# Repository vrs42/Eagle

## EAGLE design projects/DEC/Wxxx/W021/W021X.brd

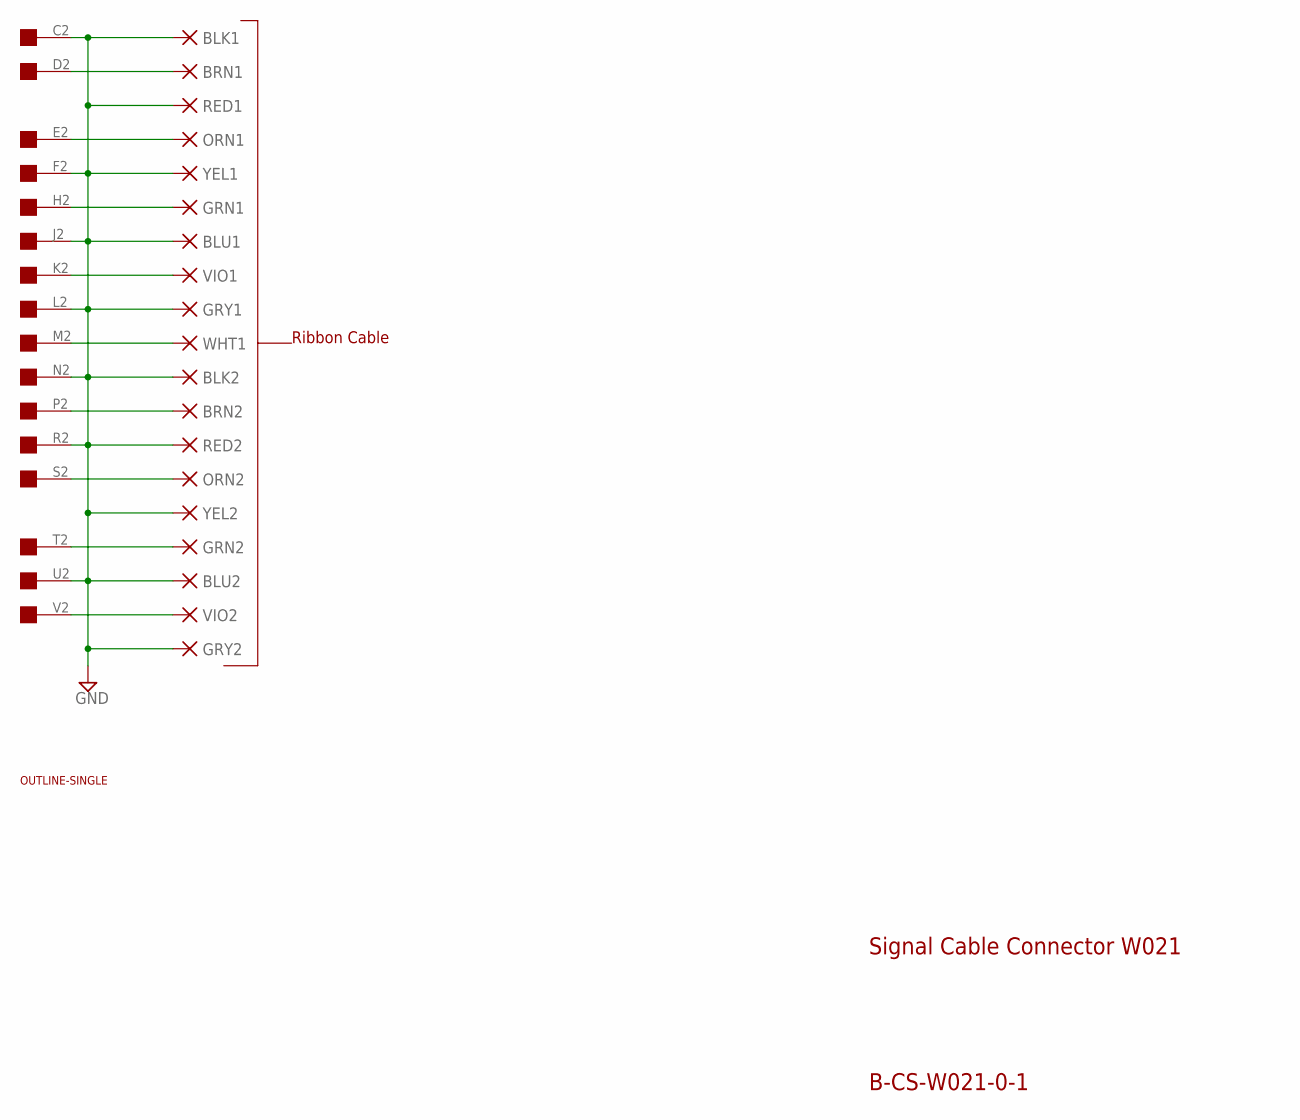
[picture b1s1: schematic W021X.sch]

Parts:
BLK1, BLK2: PAD-0465; 0465
BLU1, BLU2: PAD-0465; 0465
BRN1, BRN2: PAD-0465; 0465
GRN1, GRN2: PAD-0465; 0465
GRY1, GRY2: PAD-0465; 0465
ORN1, ORN2: PAD-0465; 0465
RED1, RED2: PAD-0465; 0465
U$1: OUTLINE-SINGLE; SINGLE
U$2: EDGE-1; EDGE-CON1
VIO1, VIO2: PAD-0465; 0465
WHT1: PAD-0465; 0465
YEL1, YEL2: PAD-0465; 0465

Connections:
GND: BLK1.P$1, BLK2.P$1, BLU1.P$1, BLU2.P$1, GRY1.P$1, GRY2.P$1, RED1.P$1, RED2.P$1, U$2.C2, U$2.F2, U$2.J2, U$2.L2, U$2.N2, U$2.R2, U$2.U2, YEL1.P$1, YEL2.P$1
unnamed: ORN1.P$1, U$2.E2
unnamed: GRN1.P$1, U$2.H2
unnamed: U$2.K2, VIO1.P$1
unnamed: U$2.M2, WHT1.P$1
unnamed: BRN2.P$1, U$2.P2
unnamed: ORN2.P$1, U$2.S2
unnamed: GRN2.P$1, U$2.T2
unnamed: U$2.V2, VIO2.P$1
unnamed: BRN1.P$1, U$2.D2

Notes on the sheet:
Signal Cable Connector W021
B-CS-W021-0-1
Ribbon Cable

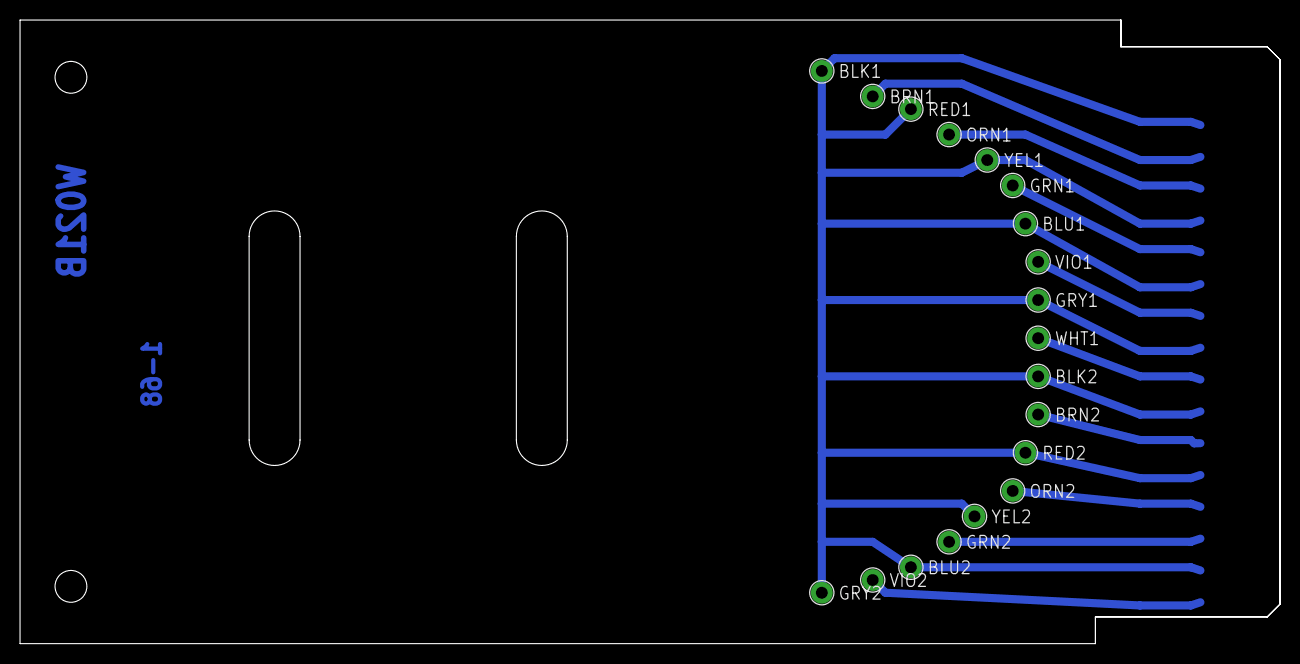
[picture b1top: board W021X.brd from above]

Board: 2 copper layers, 125.7 x 62.2 mm, 21 parts (0 on the bottom side), 10 nets.

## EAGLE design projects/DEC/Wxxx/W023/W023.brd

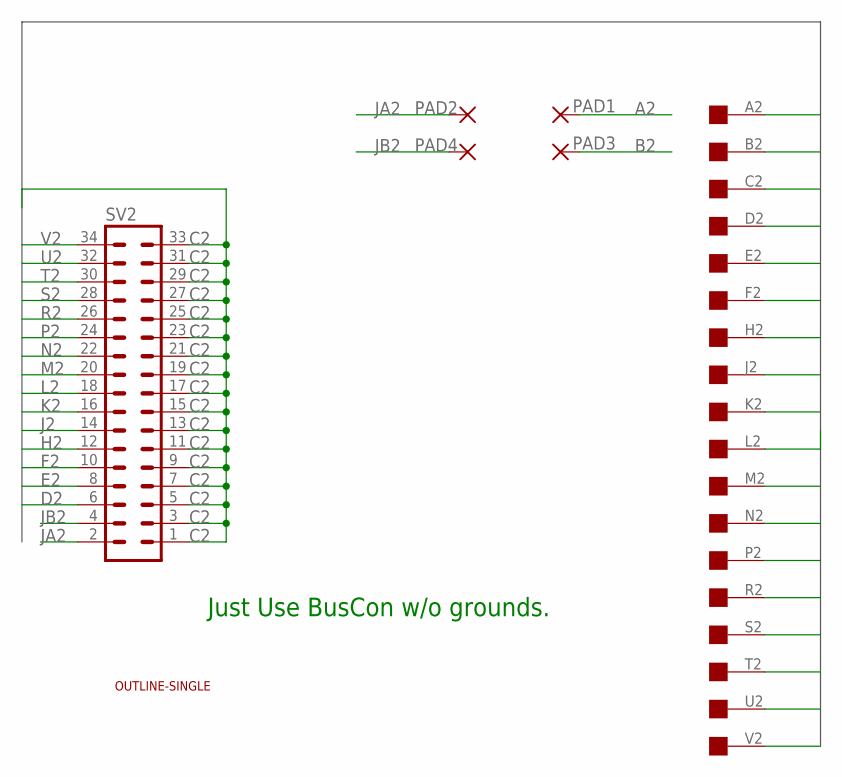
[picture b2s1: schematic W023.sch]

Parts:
PAD1, PAD2, PAD3, PAD4: 1,6/0,8
SV2: MA17-2
U$1: EDGE-1; EDGE-CON1
U$2: OUTLINE-SINGLE; SINGLE

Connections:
A2: PAD1.1, U$1.A2
B2: PAD3.1, U$1.B2
C2: SV2.1, SV2.3, SV2.5, SV2.7, SV2.9, SV2.11, SV2.13, SV2.15, SV2.17, SV2.19, SV2.21, SV2.23, SV2.25, SV2.27, SV2.29, SV2.31, SV2.33, U$1.C2
D2: SV2.6, U$1.D2
E2: SV2.8, U$1.E2
F2: SV2.10, U$1.F2
H2: SV2.12, U$1.H2
J2: SV2.14, U$1.J2
JA2: PAD2.1, SV2.2
JB2: PAD4.1, SV2.4
K2: SV2.16, U$1.K2
L2: SV2.18, U$1.L2
M2: SV2.20, U$1.M2
N2: SV2.22, U$1.N2
P2: SV2.24, U$1.P2
R2: SV2.26, U$1.R2
S2: SV2.28, U$1.S2
T2: SV2.30, U$1.T2
U2: SV2.32, U$1.U2
V2: SV2.34, U$1.V2

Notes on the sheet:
Just Use BusCon w/o grounds.

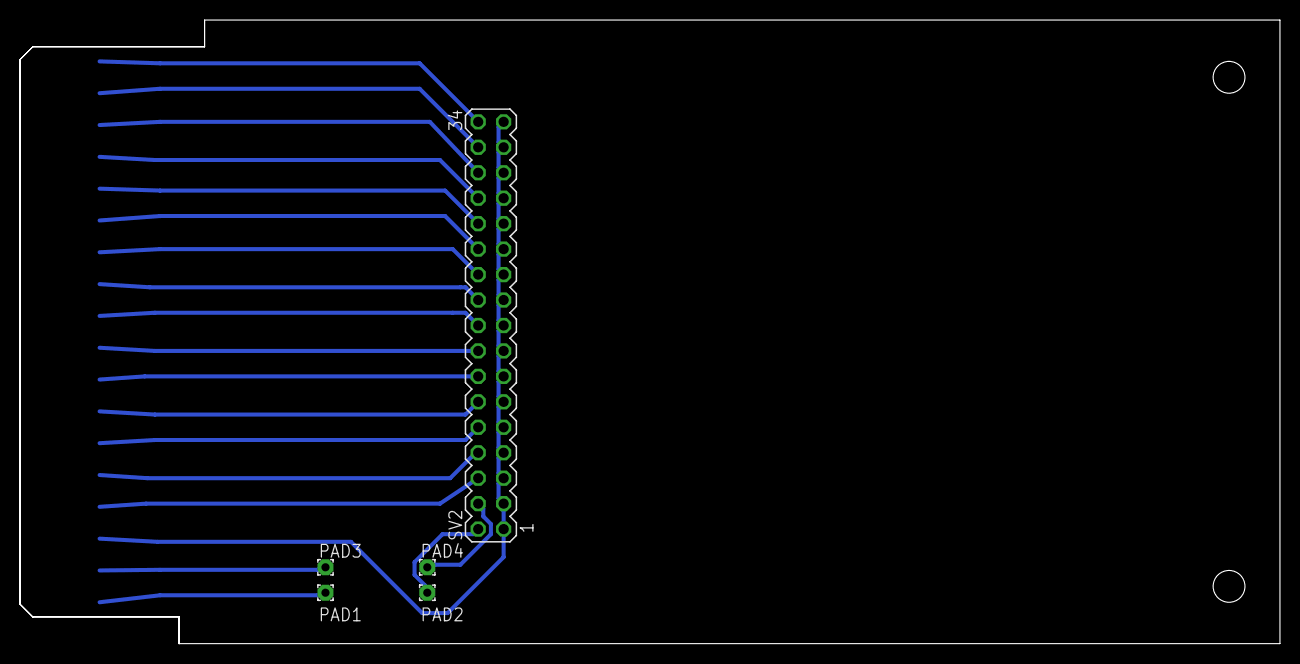
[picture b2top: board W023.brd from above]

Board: 2 copper layers, 125.7 x 62.2 mm, 7 parts (0 on the bottom side), 20 nets.

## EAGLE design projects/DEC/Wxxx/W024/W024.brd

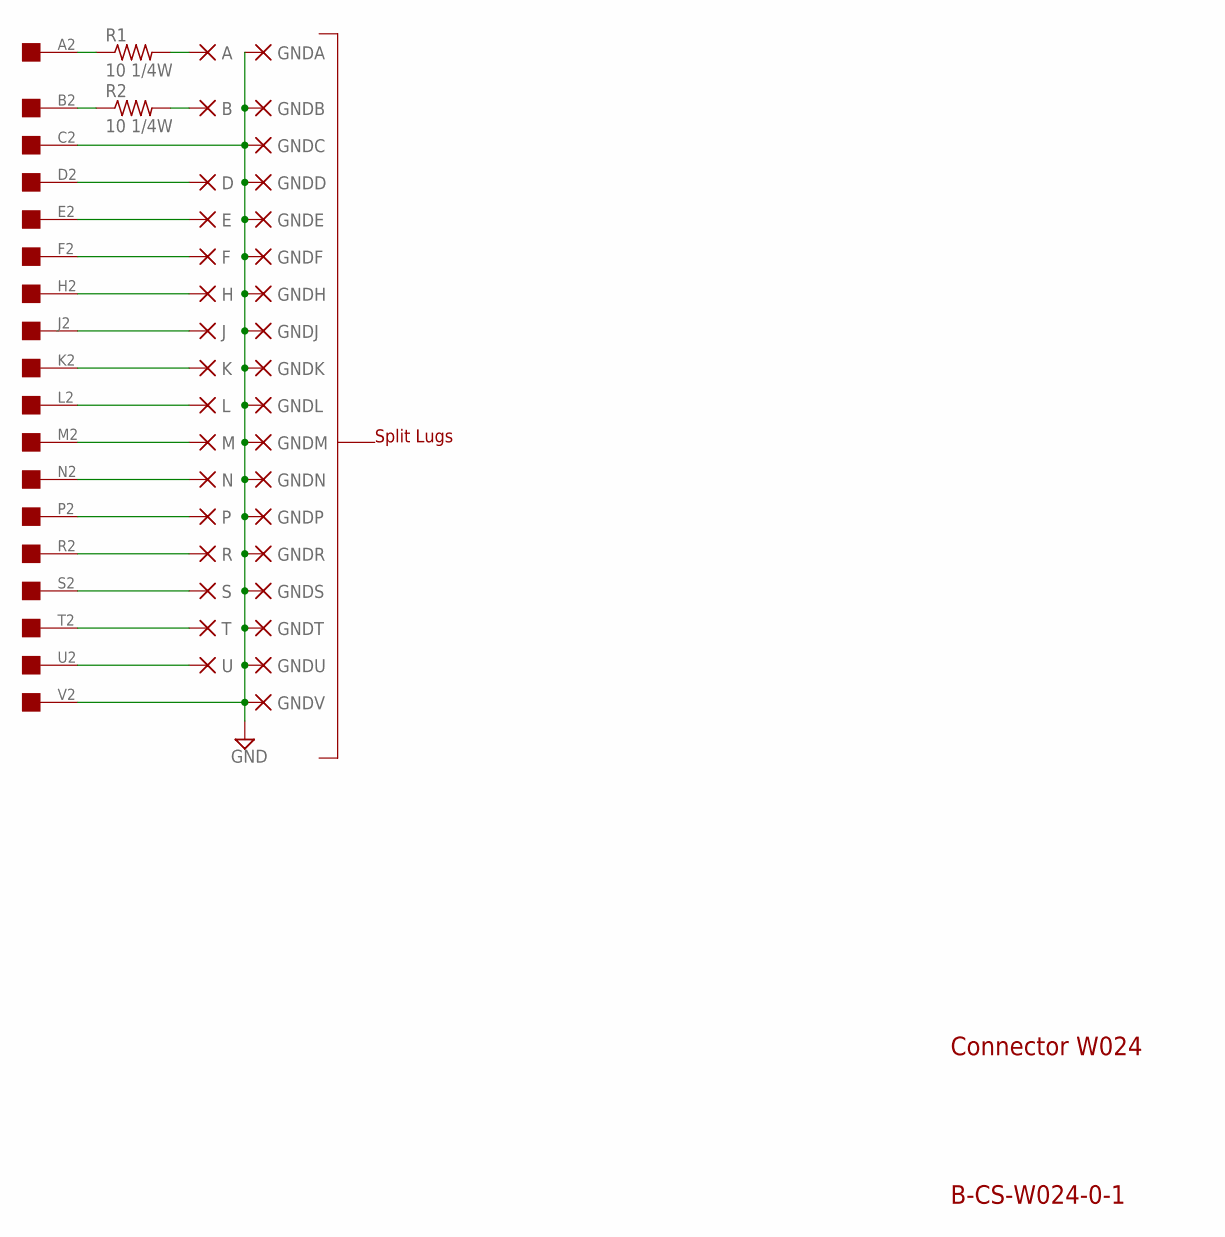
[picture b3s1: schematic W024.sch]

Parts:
A: PAD-0465; 0465
B: PAD-0465; 0465
D: PAD-0465; 0465
E: PAD-0465; 0465
F: PAD-0465; 0465
GNDA: PAD-0465; 0465
GNDB: PAD-0465; 0465
GNDC: PAD-0465; 0465
GNDD: PAD-0465; 0465
GNDE: PAD-0465; 0465
GNDF: PAD-0465; 0465
GNDH: PAD-0465; 0465
GNDJ: PAD-0465; 0465
GNDK: PAD-0465; 0465
GNDL: PAD-0465; 0465
GNDM: PAD-0465; 0465
GNDN: PAD-0465; 0465
GNDP: PAD-0465; 0465
GNDR: PAD-0465; 0465
GNDS: PAD-0465; 0465
GNDT: PAD-0465; 0465
GNDU: PAD-0465; 0465
GNDV: PAD-0465; 0465
H: PAD-0465; 0465
J: PAD-0465; 0465
K: PAD-0465; 0465
L: PAD-0465; 0465
M: PAD-0465; 0465
N: PAD-0465; 0465
P: PAD-0465; 0465
R: PAD-0465; 0465
R1, R2: 10 1/4W; 0207/10
S: PAD-0465; 0465
T: PAD-0465; 0465
U: PAD-0465; 0465
U$2: EDGE-1; EDGE-CON1

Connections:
GND: GNDA.P$1, GNDB.P$1, GNDC.P$1, GNDD.P$1, GNDE.P$1, GNDF.P$1, GNDH.P$1, GNDJ.P$1, GNDK.P$1, GNDL.P$1, GNDM.P$1, GNDN.P$1, GNDP.P$1, GNDR.P$1, GNDS.P$1, GNDT.P$1, GNDU.P$1, GNDV.P$1, U$2.C2, U$2.V2
unnamed: E.P$1, U$2.E2
unnamed: H.P$1, U$2.H2
unnamed: K.P$1, U$2.K2
unnamed: M.P$1, U$2.M2
unnamed: P.P$1, U$2.P2
unnamed: S.P$1, U$2.S2
unnamed: T.P$1, U$2.T2
unnamed: D.P$1, U$2.D2
unnamed: R2.1, U$2.B2
unnamed: R1.1, U$2.A2
unnamed: A.P$1, R1.2
unnamed: B.P$1, R2.2
unnamed: F.P$1, U$2.F2
unnamed: J.P$1, U$2.J2
unnamed: L.P$1, U$2.L2
unnamed: N.P$1, U$2.N2
unnamed: R.P$1, U$2.R2
unnamed: U.P$1, U$2.U2

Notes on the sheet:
Connector W024
B-CS-W024-0-1
Split Lugs

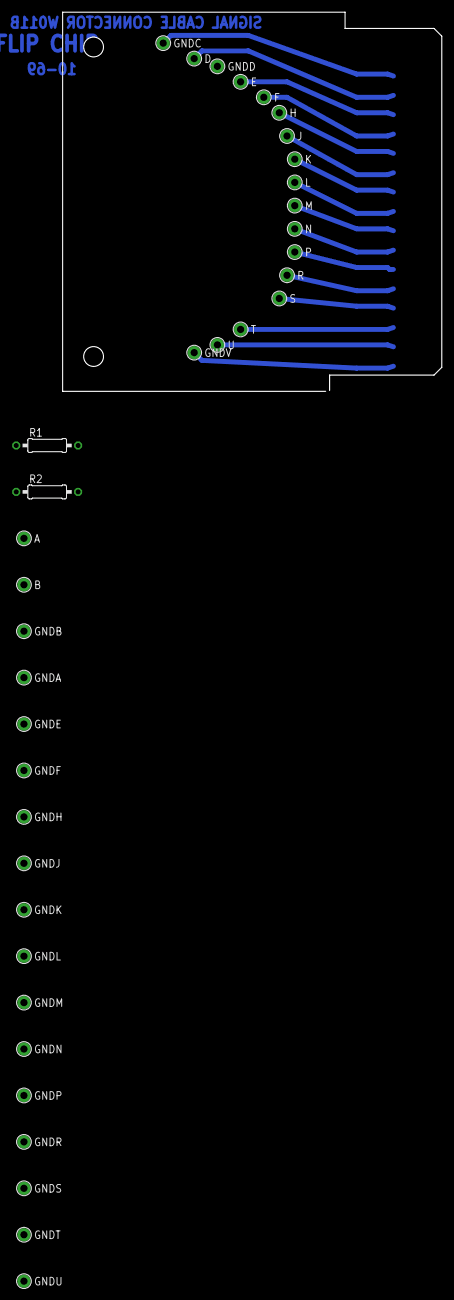
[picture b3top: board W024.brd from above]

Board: 2 copper layers, 62.2 x 62.2 mm, 37 parts (0 on the bottom side), 19 nets.
